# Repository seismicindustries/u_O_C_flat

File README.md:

# u_O_C_flat

same as the original

with the same formfactor as the u_O_C but different placement of the encoders and buttons

also the linear regulator has been replaced by a MP1469 regulator.

-> so far the design is untested. i made some PCB but i don't have my display yet...

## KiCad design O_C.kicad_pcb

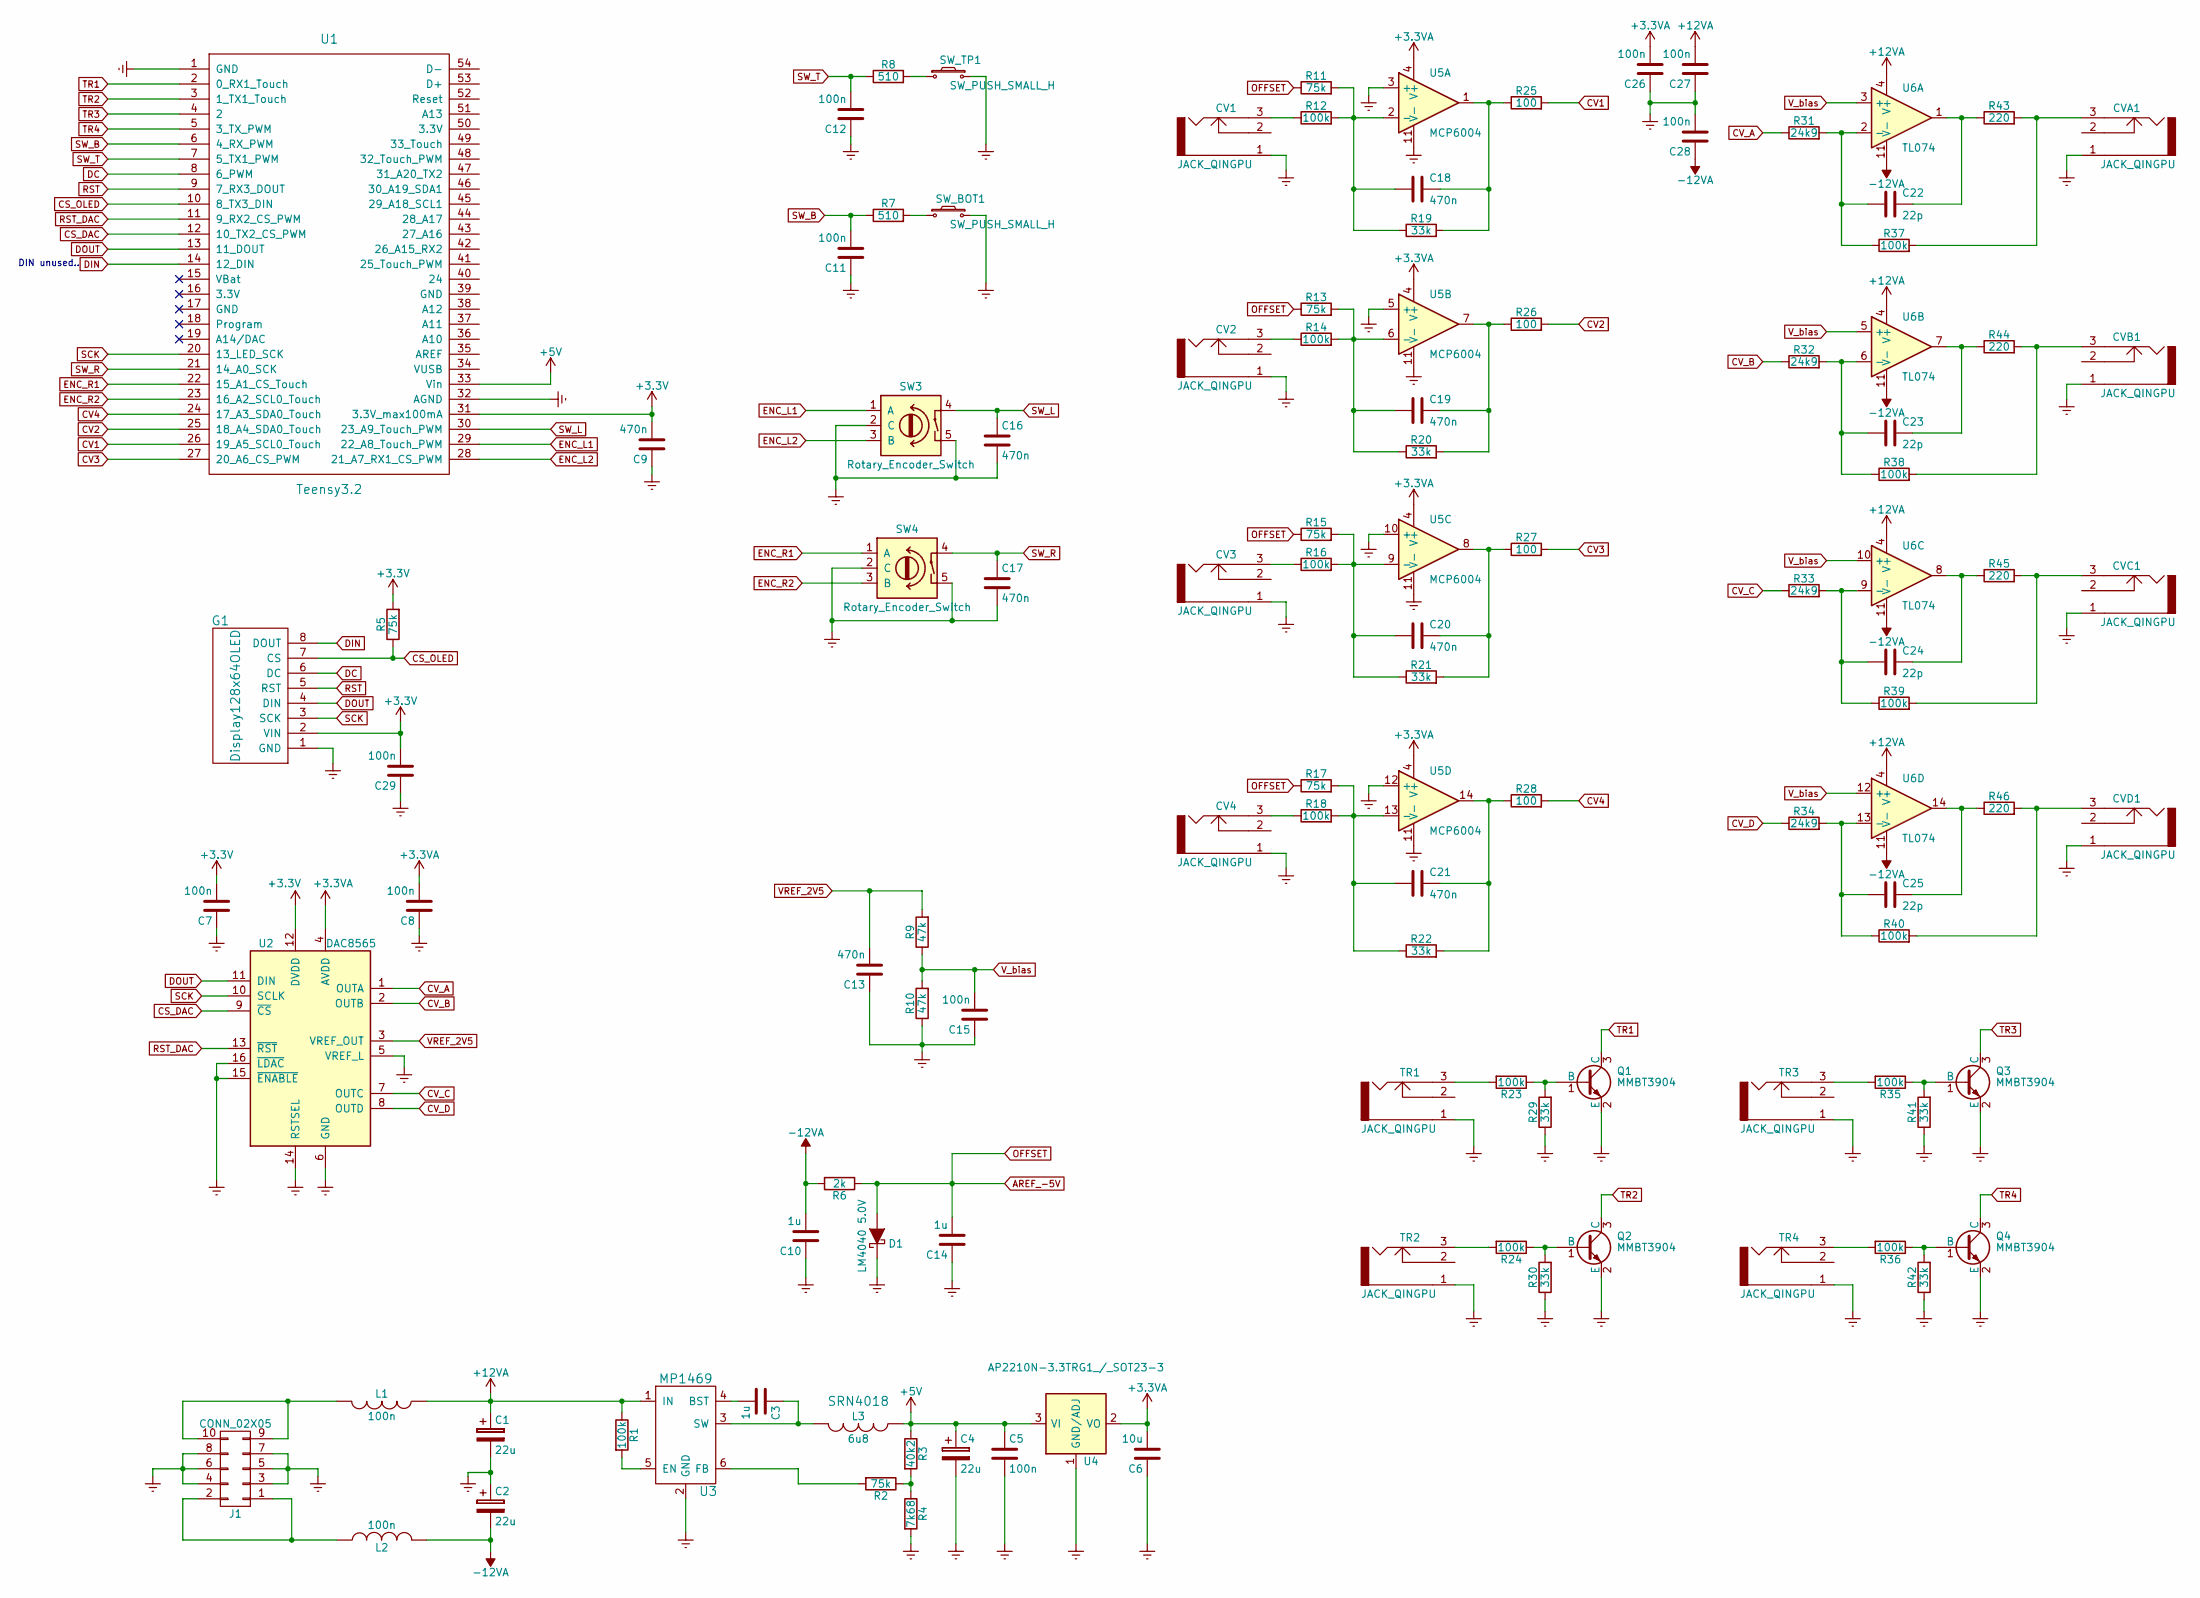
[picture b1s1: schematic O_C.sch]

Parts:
C1, C2, C4: 22u; CP_Elec_7.3x4.3; MPN EEF-CX1D220R
C3, C10, C14: 1u; C_0603; MPN GCJ188R71E105KA01D
C5, C7, C8, C11, C12, C15, C26, C27, C28, C29: 100n; C_0603; MPN C0603C104Z3VACTU
C6: 10u; C_0603; MPN C1608X5R0J106M080AB
C9, C13, C16, C17, C18, C19, C20, C21: 470n; C_0603; MPN EMK107B7474KA-T
C22, C23, C24, C25: 22p; C_0603; MPN C0603C220J5GACTU
CV1, CV2, CV3, CV4: JACK_QINGPU; jack_qingpu
CVA1: JACK_QINGPU; jack_qingpu
CVB1: JACK_QINGPU; jack_qingpu
CVC1: JACK_QINGPU; jack_qingpu
CVD1: JACK_QINGPU; jack_qingpu
D1: LM4040 5.0V; SOT-23; MPN LM4040C50IDBZR
G1: Display128x64OLED; OLED_DISPLAY_128_64_1_3_inch
J1: CONN_02X05; Pin_Header_Angled_2x05_Pitch2.54mm_with_space_for_con; MPN 649-68020-110HLF
L1, L2: 100n; Inductor_PSU_NLCV32T; MPN NLCV32T-R10M-PFR
L3: 6u8; Inductor_SRN4018TA_bourns; MPN SRN4018TA-6R8M
Q1, Q2, Q3, Q4: MMBT3904; SOT-23; MPN MMBT3904,215
R1, R12, R14, R16, R18, R23, R24, R35, R36, R37, R38, R39, R40: 100k; R_0603; MPN RCA0603100KJNEC
R2, R5, R11, R13, R15, R17: 75k; R_0603; MPN CR0603-FX-2202ELF
R3: 40k2; R_0603
R4: 7k68; R_0603
R6: 2k; R_0603; MPN RC0603FR-0724K9L
R7, R8: 510; R_0603; MPN RC0603FR-07510RL
R9, R10: 47k; R_0603; MPN RC0603FR-0747KL
R19, R20, R21, R22, R29, R30, R41, R42: 33k; R_0603; MPN ERJ-3GEYJ333V
R25, R26, R27, R28: 100; R_0603
R31, R32, R33, R34: 24k9; R_0603; MPN RC0603FR-0724K9L
R43, R44, R45, R46: 220; R_0603; MPN CRCW0603220RFKEB
SW3, SW4: Rotary_Encoder_Switch; ENCODER_PEC11_SMD; MPN PEC11S-9215K-H0015
SW_BOT1: SW_PUSH_SMALL_H; APEM_tactile_SMD_switch_6mm; MPN ADTSM66NV
SW_TP1: SW_PUSH_SMALL_H; APEM_tactile_SMD_switch_6mm; MPN ADTSM66NV
TR1, TR2, TR3, TR4: JACK_QINGPU; jack_qingpu
U1: Teensy3.2; Teensy_3_2; MPN DEV-13736
U2: DAC8565; TSSOP-16_4.4x5mm_Pitch0.65mm; MPN DAC8565ICPW
U3: MP1469; SOT-23-6; MPN MP1469GJ-Z
U4: AP2210N-3.3TRG1_/_SOT23-3; SOT-23; MPN AP2210N-3.3TRG1
U5: MCP6004; TSSOP-14_4.4x5mm_Pitch0.65mm; MPN MCP6004T-I/ST
U6: TL074; TSSOP-14_4.4x5mm_Pitch0.65mm; MPN TL074CPWR

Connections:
+3.3VA: C6.2, C8.2, C26.2, U2.4 (AVDD), U4.2 (VO), U5.4 (V+)
+3V3: C7.2, C9.2, C29.2, G1.2 (VIN), R5.2, U1.31 (3.3V_max100mA), U2.12 (DVDD)
+5V: C4.1, C5.1, L3.1, R3.1, U1.33 (Vin), U4.3 (VI)
+12VA: C1.1, C27.2, L1.1, R1.1, U3.1 (IN), U6.4 (V+)
-12VA: C2.2, C10.2, C28.1, L2.2, R6.2, U6.11 (V-)
AREF_-5V: C14.2, D1.2 (A), R6.1, R11.1, R13.1, R15.1, R17.1
CS_DAC: U1.12 (10_TX2_CS_PWM), U2.9 (~CS)
CS_OLED: G1.7 (CS), R5.1, U1.10 (8_TX3_DIN)
CV1: R25.2, U1.26 (19_A5_SCL0_Touch)
CV2: R26.2, U1.25 (18_A4_SDA0_Touch)
CV3: R27.2, U1.27 (20_A6_CS_PWM)
CV4: R28.2, U1.24 (17_A3_SDA0_Touch)
CV_A: R31.1, U2.1 (OUTA)
CV_B: R32.1, U2.2 (OUTB)
CV_C: R33.1, U2.7 (OUTC)
CV_D: R34.1, U2.8 (OUTD)
DC: G1.6 (DC), U1.8 (6_PWM)
DIN: G1.8 (DOUT), U1.14 (12_DIN)
DOUT: G1.4 (DIN), U1.13 (11_DOUT), U2.11 (DIN)
ENC_L1: SW3.1 (A), U1.29 (22_A8_Touch_PWM)
ENC_L2: SW3.3 (B), U1.28 (21_A7_RX1_CS_PWM)
ENC_R1: SW4.1 (A), U1.22 (15_A1_CS_Touch)
ENC_R2: SW4.3 (B), U1.23 (16_A2_SCL0_Touch)
Earth: C1.2, C2.1, C4.2, C5.2, C6.1, C7.1, C8.1, C9.1, C10.1, C11.1, C12.1, C13.1, C14.1, C15.1, C16.2, C17.2, C26.1, C27.1, C28.2, C29.1, CV1.1, CV2.1, CV3.1, CV4.1, CVA1.1, CVB1.1, CVC1.1, CVD1.1, D1.1 (K), G1.1 (GND), J1.3, J1.4, J1.5, J1.6, J1.7, J1.8, Q1.2 (E), Q2.2 (E), Q3.2 (E), Q4.2 (E), R4.2, R10.1, R29.1, R30.1, R41.1, R42.1, SW3.2 (C), SW3.5, SW4.2 (C), SW4.5, SW_BOT1.2, SW_TP1.2, TR1.1, TR2.1, TR3.1, TR4.1, U1.1 (GND), U1.32 (AGND), U2.5 (VREF_L), U2.6 (GND), U2.14 (RSTSEL), U2.15 (~ENABLE), U2.16 (~LDAC), U3.2 (GND), U4.1 (GND/ADJ), U5.3 (+), U5.5 (+), U5.10 (+), U5.11 (V-), U5.12 (+)
unnamed: C3.1, L3.2, U3.3 (SW)
unnamed: C3.2, U3.4 (BST)
unnamed: C18.1, R19.2, R25.1, U5.1
unnamed: C18.2, R11.2, R12.2, R19.1, U5.2 (-)
unnamed: C19.1, R20.2, R26.1, U5.7
unnamed: C19.2, R13.2, R14.2, R20.1, U5.6 (-)
unnamed: C20.1, R21.2, R27.1, U5.8
unnamed: C20.2, R15.2, R16.2, R21.1, U5.9 (-)
unnamed: C21.1, R22.2, R28.1, U5.14
unnamed: C21.2, R17.2, R18.2, R22.1, U5.13 (-)
unnamed: C22.1, R43.1, U6.1
unnamed: C22.2, R31.2, R37.1, U6.2 (-)
unnamed: C23.1, R44.1, U6.7
unnamed: C23.2, R32.2, R38.1, U6.6 (-)
unnamed: C24.1, R45.1, U6.8
unnamed: C24.2, R33.2, R39.1, U6.9 (-)
unnamed: C25.1, R46.1, U6.14
unnamed: C25.2, R34.2, R40.1, U6.13 (-)
unnamed: CV1.3, R12.1
unnamed: CV2.3, R14.1
unnamed: CV3.3, R16.1
unnamed: CV4.3, R18.1
unnamed: CVA1.3, R37.2, R43.2
unnamed: CVB1.3, R38.2, R44.2
unnamed: CVC1.3, R39.2, R45.2
unnamed: CVD1.3, R40.2, R46.2
unnamed: J1.1, J1.2, L2.1
unnamed: J1.9, J1.10, L1.2
unnamed: Q1.1 (B), R23.1, R29.2
unnamed: Q2.1 (B), R24.1, R30.2
unnamed: Q3.1 (B), R35.1, R41.2
unnamed: Q4.1 (B), R36.1, R42.2
unnamed: R1.2, U3.5 (EN)
unnamed: R2.1, R3.2, R4.1
unnamed: R2.2, U3.6 (FB)
unnamed: R7.2, SW_BOT1.1
unnamed: R8.2, SW_TP1.1
unnamed: R23.2, TR1.3
unnamed: R24.2, TR2.3
unnamed: R35.2, TR3.3
unnamed: R36.2, TR4.3
RST: G1.5 (RST), U1.9 (7_RX3_DOUT)
RST_DAC: U1.11 (9_RX2_CS_PWM), U2.13 (~RST)
SCK: G1.3 (SCK), U1.20 (13_LED_SCK), U2.10 (SCLK)
SW_B: C11.2, R7.1, U1.6 (4_RX_PWM)
SW_L: C16.1, SW3.4, U1.30 (23_A9_Touch_PWM)
SW_R: C17.1, SW4.4, U1.21 (14_A0_SCK)
SW_T: C12.2, R8.1, U1.7 (5_TX1_PWM)
TR1: Q1.3 (C), U1.2 (0_RX1_Touch)
TR2: Q2.3 (C), U1.3 (1_TX1_Touch)
TR3: Q3.3 (C), U1.4 (2)
TR4: Q4.3 (C), U1.5 (3_TX_PWM)
VREF_2V5: C13.2, R9.2, U2.3 (VREF_OUT)
V_bias: C15.2, R9.1, R10.2, U6.3 (+), U6.5 (+), U6.10 (+), U6.12 (+)

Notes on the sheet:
DIN unused..

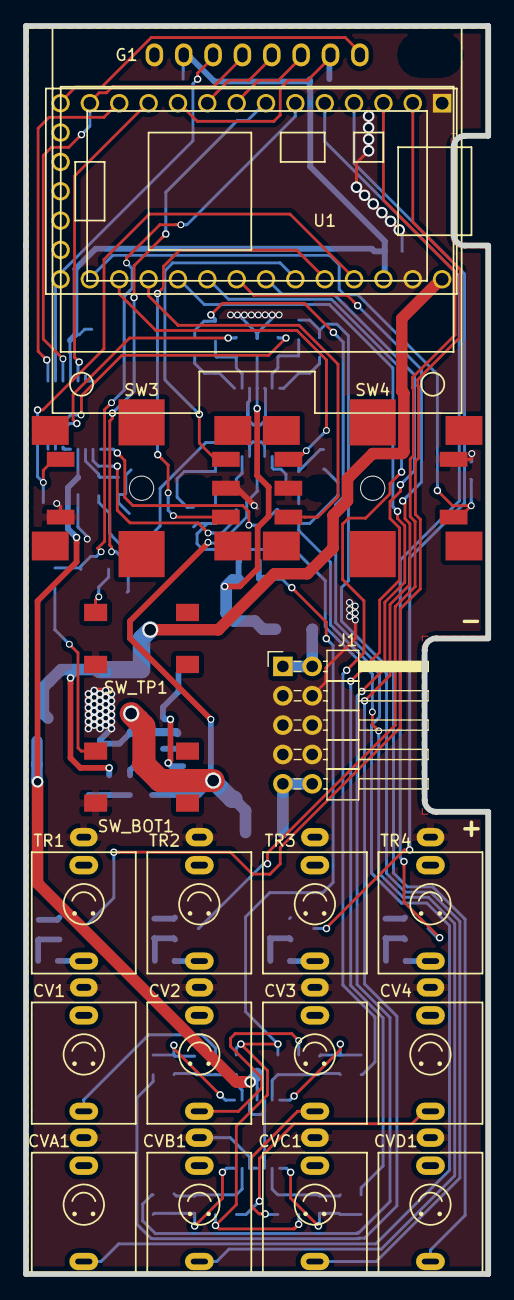
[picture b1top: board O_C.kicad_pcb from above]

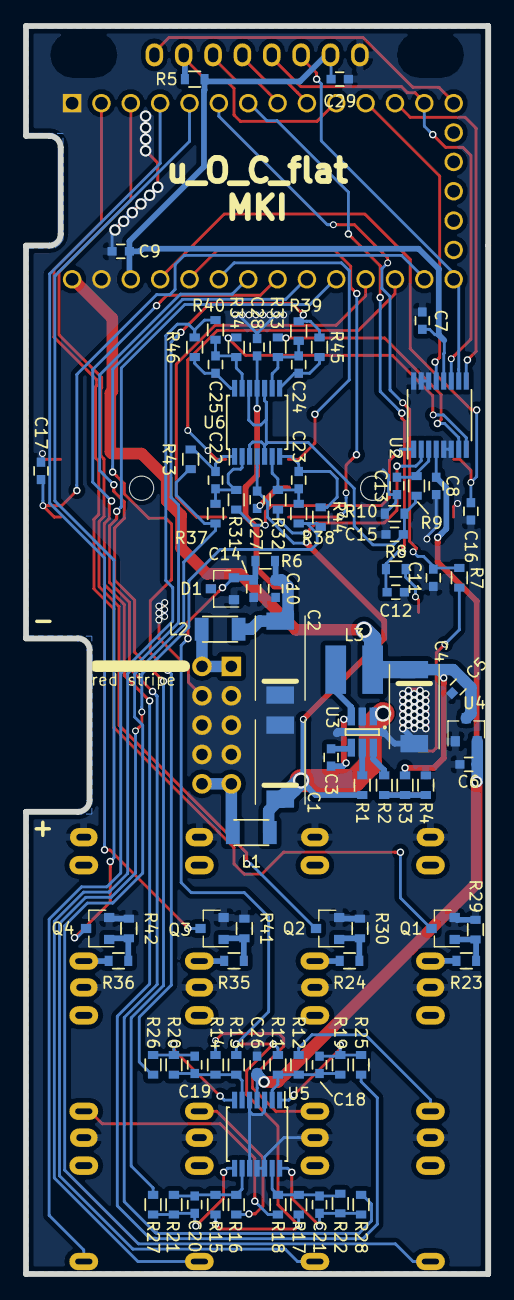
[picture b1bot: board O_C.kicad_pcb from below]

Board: 2 copper layers, 40.0 x 108.0 mm, 107 parts (88 on the bottom side), 78 nets.

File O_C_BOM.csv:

Refs,Value,Footprint,MFR,MPN,SPR,QTY,SPNSW_BOT1;SW_TP1,SW_PUSH_SMALL_H,raffilibkicad:APEM_tactile_SMD_switch_6mm,APEM,ADTSM66NV,Mouser,2,642-ADTSM66NVC1;C2;C4,22u,raffilibkicad:CP_Elec_7.3x4.3,Panasonic,EEF-CX1D220R,Mouser,3,667-EEF-CX1D220RC5;C7;C8;C12;C11;C15;C26;C28;C27;C29,100n,raffilibkicad:C_0603,Wurth Electronics,8.85012E+11,Mouser,10,710-885012206095C6,10u,raffilibkicad:C_0603,TDK,C1608X5R0J106M080AB,Mouser,1,810-C1608X5R0J106MC3;C10;C14,1u,raffilibkicad:C_0603,Murata,GCJ188R71E105KA01D,Mouser,3,81-GCJ188R71E105KA1DC22;C23;C24;C25,22p,raffilibkicad:C_0603,Kemet,C0603C220J5GACTU,Mouser,4,80-C0603C220J5GC9;C16;C17;C18;C19;C20;C21;C13,470n,raffilibkicad:C_0603,Taiyo Yuden,EMK107B7474KA-T,Mouser,8,963-EMK107B7474KA-TSW3;SW4,Rotary_Encoder_Switch,raffilibkicad:ENCODER_PEC11_SMD,Bourns,PEC11S-9215K-H0015,Mouser,2,652-PEC11S9215KH0015L1;L2,100n,raffilibkicad:Inductor_PSU_NLCV32T,TDK,NLCV32T-R10M-PFR,Mouser,2,810-NLCV32T-R10M-PFRL3,6u8,raffilibkicad:Inductor_SRN4018TA_bourns,Bourns,SRN4018TA-6R8M,Mouser,1,652-SRN4018TA-6R8MG1,Display128x64OLED,raffilibkicad:OLED_DISPLAY_128_64_1_3_inch,,,,1,J1,CONN_02X05,raffilibkicad:Pin_Header_Angled_2x05_Pitch2.54mm_with_space_for_con,Amphenol FCI,649-68020-110HLF,Mouser,1,68020-110HLFR25;R26;R27;R28,100,raffilibkicad:R_0603,,,Mouser,4,603-RC0603FR-07100RLR1;R23;R24;R35;R36;R12;R14;R16;R18;R37;R38;R39;R40,100k,raffilibkicad:R_0603,Vishay / Draloric,RCA0603100KJNEC,Mouser,13,71-RCA0603100KJNECR43;R44;R45;R46,220,raffilibkicad:R_0603,Vishay,CRCW0603220RFKEB,Mouser,4,71-CRCW0603220RFKEBR31;R32;R33;R34,24k9,raffilibkicad:R_0603,Yageo,RC0603FR-0724K9L,Mouser,4,603-RC0603FR-0724K9LR6,2k,raffilibkicad:R_0603,Yageo,RC0603FR-0724K9L,Mouser,1,603-RC0603FR-072KLR29;R30;R41;R42;R19;R20;R21;R22,33k,raffilibkicad:R_0603,Panasonic,ERJ-3GEYJ333V,Mouser,8,667-ERJ-3GEYJ333VR3,40k2,raffilibkicad:R_0603,,,Mouser,1,603-RC0805FR-0740K2LR9;R10,47k,raffilibkicad:R_0603,Yageo,RC0603FR-0747KL,Mouser,2,603-RC0603FR-0747KLR8;R7,510,raffilibkicad:R_0603,Yageo,RC0603FR-07510RL,Mouser,2,603-RC0603FR-07510RLR2;R5;R11;R13;R15;R17,75k,raffilibkicad:R_0603,Bourns,CR0603-FX-2202ELF,Mouser,6,652-CR0603FX-2202ELFR4,7k68,raffilibkicad:R_0603,,,Mouser,1,603-RC0805FR-077K68LU4,AP2210N-3.3TRG1_/_SOT23-3,raffilibkicad:SOT-23,Diodes Incorporated,AP2210N-3.3TRG1,Mouser,1,621-AP2210N-3.3TRG1D1,LM4040 5.0V,raffilibkicad:SOT-23,Texas Instruments,LM4040C50IDBZR,Mouser,1,595-LM4040C50IDBZRQ1;Q2;Q3;Q4,MMBT3904,raffilibkicad:SOT-23,Nexperia,"MMBT3904,215",Mouser,4,771-MMBT3904T/RU3,MP1469,raffilibkicad:SOT-23-6,MPS,MP1469GJ-Z,Mouser,1,946-MP1469GJZU5,MCP6004,raffilibkicad:TSSOP-14_4.4x5mm_Pitch0.65mm,Microchip,MCP6004T-I/ST,Mouser,1,579-MCP6004T-I/STU6,TL074,raffilibkicad:TSSOP-14_4.4x5mm_Pitch0.65mm,Texas Instruments,TL074CPWR,Mouser,1,595-TL074CPWRU2,DAC8565,raffilibkicad:TSSOP-16_4.4x5mm_Pitch0.65mm,Texas Instruments,DAC8565ICPW,Mouser,1,595-DAC8565ICPWU1,Teensy3.2,raffilibkicad:Teensy_3_2,SparkFun,DEV-13736,Mouser,1,474-DEV-13736TR4;TR3;TR2;TR1;CVD1;CVC1;CVB1;CVA1;CV4;CV3;CV2;CV1,JACK_QINGPU,raffilibkicad:jack_qingpu,,,,12,

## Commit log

2018-02-18 first commit MK1
2018-02-18 pic added
2018-02-18 pic url changed
2018-02-18 agaaain
2018-02-18 some text that its untested, yet
